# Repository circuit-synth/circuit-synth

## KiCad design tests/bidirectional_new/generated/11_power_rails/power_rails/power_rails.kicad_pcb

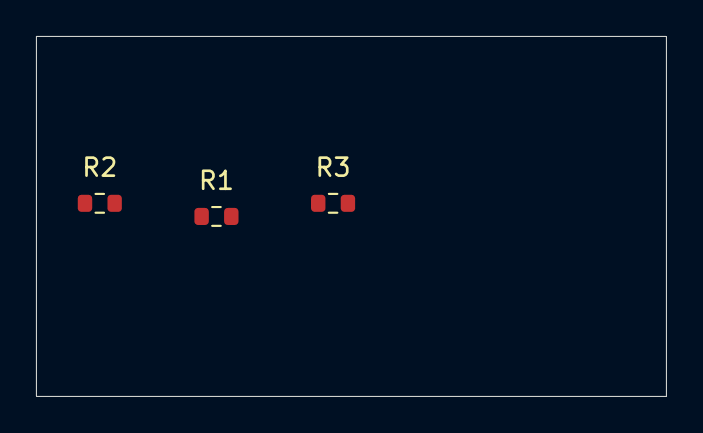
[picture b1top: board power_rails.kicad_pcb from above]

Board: 2 copper layers, 35.0 x 20.0 mm, 3 parts (0 on the bottom side), 2 nets, no tracks yet.

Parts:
R1: 10k; R_0603_1608Metric
R2: 20k; R_0603_1608Metric
R3: 30k; R_0603_1608Metric

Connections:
GND: R1.1, R2.1, R3.1
VCC: R1.2, R2.2, R3.2
